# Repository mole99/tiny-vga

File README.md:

# Tiny VGA 

Tiny VGA is a Pmod peripheral designed for [Tiny Tapeout](https://tinytapeout.com/), but can of course also be used with any other Pmod compatible hardware such as certain FPGA boards.

View the schematic online using [KiCanvas](https://kicanvas.org/?github=https%3A%2F%2Fgithub.com%2Fmole99%2Ftiny-vga%2Fblob%2Fmain%2Fpcb%2Ftiny-vga.kicad_sch)!

**Why Yet Another Pmod VGA Peripheral?**

Tiny VGA only needs one Pmod connector to work. This means if you choose to use the output Pmod of the Tiny Tapeout PCB to connect to Tiny VGA, you still have the bidirectional and input Pmod available for other purposes.

It defines an interface for 2-bit per color VGA, so you can easily try other Tiny Tapeout designs that use the Tiny VGA pinout.

The board is designed in [KiCad](https://www.kicad.org/) and uses the [KiCAD JLCPCB tools](https://github.com/Bouni/kicad-jlcpcb-tools) to manage the assignment of components from the JLCPCB parts library.

## How Do I Get One? 

I do not sell Tiny VGAs, but you can order a few Tiny VGAs directly from PCB manufacturers for relatively little money. the cost per PCB gets cheaper if you order, say, ten at a time. You could give away the remaining Tiny VGAs to others who are located near you to help out the community :)

Search the Tiny Tapeout Discord server for others who could use one.

## Ordering Tiny VGA at JLCPCB

I have designed Tiny VGA so that it can be easily ordered fully-manufactured from JLCPCB. I am not sponsored or affiliated with JLCPCB in any way. If you would like to make it possible to produce Tiny VGA with other PCB manufacturers, you are welcome to contribute!

The [KiCAD JLCPCB tools](https://github.com/Bouni/kicad-jlcpcb-tools) needs to be installed to create the production files. Or you can use them right away under `pcb/jlcpcb/production_files/`.

1. Go to [JLCPCB](https://jlcpcb.com/) and create an account. 
2. Upload the gerber files from `pcb/jlcpcb/production_files/GERBER-tiny-vga.zip`.
3. You will get various options to choose from and a price offer. You don't really need to change anything, but you could change the quantity, choose a different color for the PCB and remove the order number.
3. Next, enable "PCB Assembly", keep the settings as they are and confirm. You will be forwarded to a new page with a view of the PCB. 
4. Click on "Next" and you will be prompted to upload the BOM and CPL file which you can find under `pcb/jlcpcb/production_files/BOM-tiny-vga.csv` and `pcb/jlcpcb/production_files/CPL-tiny-vga.csv`. 
5. The next page shows you all the parts that will be placed. 
6. Again, "Next" will lead you to the component placement page where you can confirm the placement of the parts. Here you might need to rotate some of the components.
7. Click on "Next" and you will get your quote for the assembled PCBs. Proceed to the checkout and you are done :D

## Tiny VGA Pinout

Pin numbering according to Pmod specification.

| Pin | Signal | Pin | Signal |
| :-: | :----: | :-: | :----: |
| top row    | | bottom row | |
| 1   | R1     | 7   | R0     |
| 2   | G1     | 8   | G0     |
| 3   | B1     | 9   | B0     |
| 4   | VS     | 10  | HS     |
| 5   | GND    | 11  | GND    |
| 6   | VCC    | 12  | VCC    |

> [!NOTE]  
> R0, G0, B0 are the least significant bits\
> R1, G1, B1 are the most significant bits\
> VS is the vertical sync\
> HS is the horizontal sync\
> VCC must be 3V3

## Board Images

### v1.0

Tiny VGA v1.0 board manufactured by JLCPCB, including SMD components (THT connectors manually soldered).

|          |      |
|--------------|-----------|
|  |       |

### v1.2

Tiny VGA v1.2 board manufactured by JLCPCB, including SMD components and THT connectors.

|          |      |
|--------------|-----------|
|  |       |

## Demo

The demo output is 800x600 SVGA and the quality is excellent in real life.

## License

This work is licensed under a
[Creative Commons Attribution-ShareAlike 4.0 International License][cc-by-sa].

[cc-by-sa]: http://creativecommons.org/licenses/by-sa/4.0/

Copyright (c) Leo Moser

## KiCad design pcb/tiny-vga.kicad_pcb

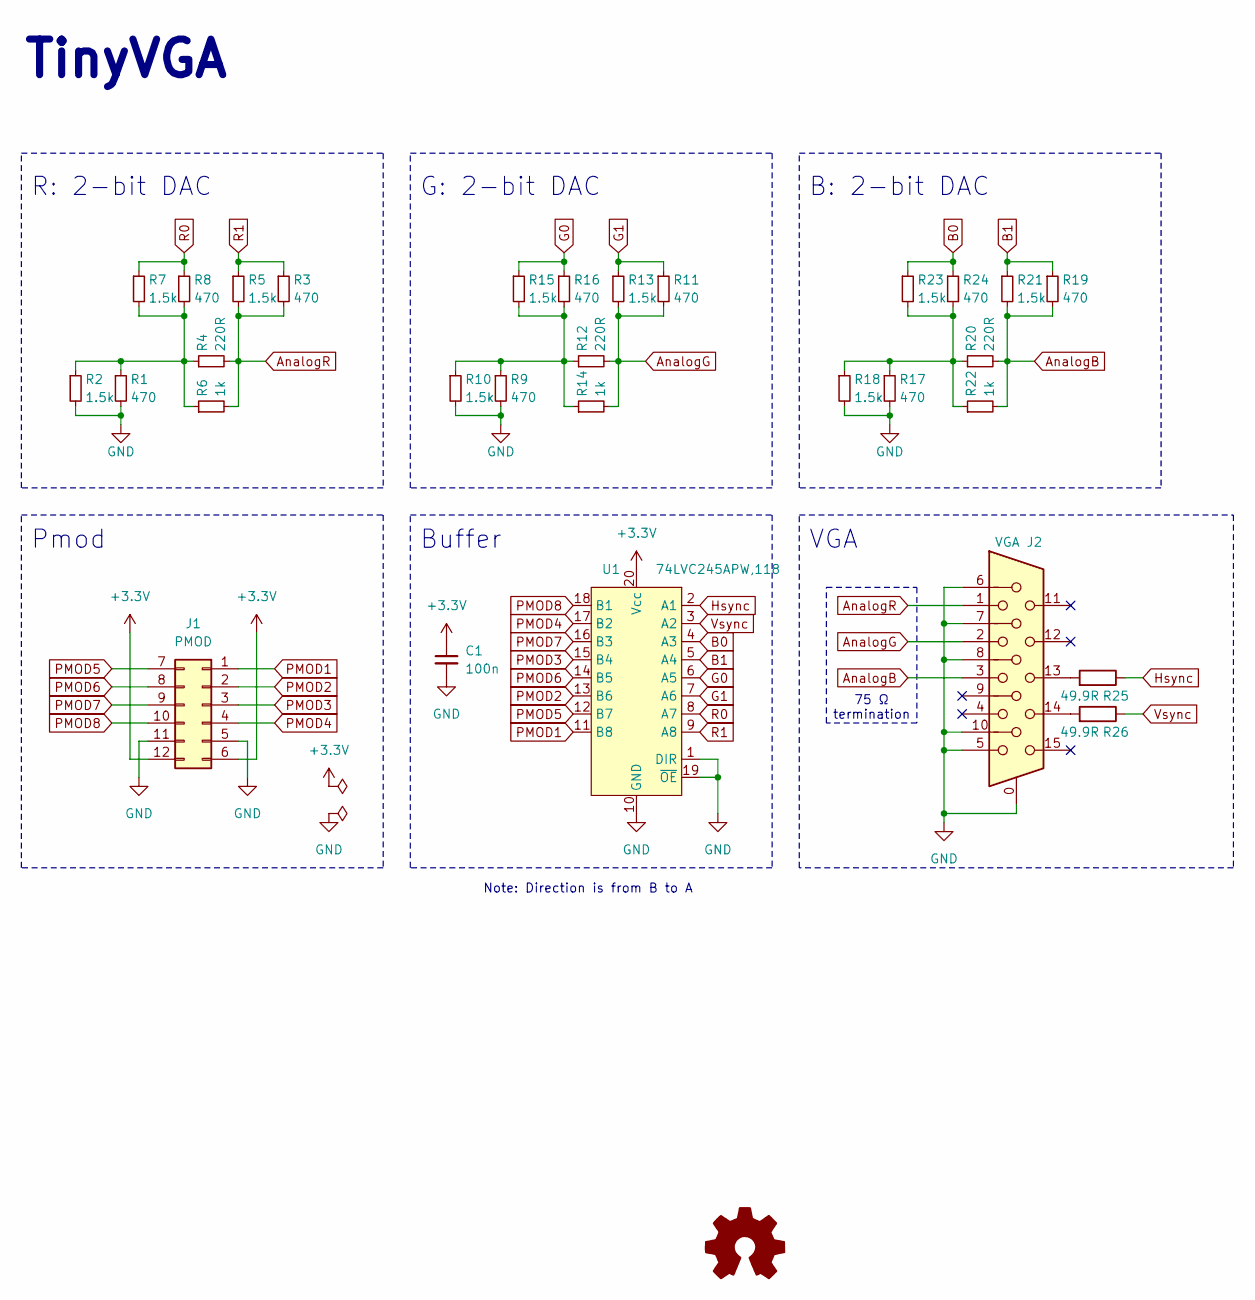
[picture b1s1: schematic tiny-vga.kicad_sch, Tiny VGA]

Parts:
C1: 100n; C_0603_1608Metric; MPN CGA3E3X7S2A104M080AB; LCSC C14663
J1: PMOD; PinHeader_2x06_P2.54mm_Horizontal; MPN 826634-6; LCSC C2935938
J2: VGA; DSUB-15-HD_Female_Horizontal_P2.29x1.98mm_EdgePinOffset8.35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; MPN L77HDE15SD1CH4FVGA; LCSC C138387
R1, R3, R8, R9, R11, R16, R17, R19, R24: 470; R_0402_1005Metric; MPN RCC0402470RFKED; LCSC C25117
R2, R5, R7, R10, R13, R15, R18, R21, R23: 1.5k; R_0402_1005Metric; MPN RCC04021K50FKED; LCSC C25867
R4, R12, R20: 220R; R_0402_1005Metric; MPN RCS0402220RFKED; LCSC C25091
R6, R14, R22: 1k; R_0402_1005Metric; MPN CRCW04021K00FKED; LCSC C11702
R25, R26: 49.9R; R_0402_1005Metric; MPN ERJ-2RKF49R9X; LCSC C25120
U1: 74LVC245APW,118; TSSOP-20_4.4x6.5mm_P0.65mm; MPN 74LVC245APW,118; LCSC C6082

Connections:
+3.3V: C1.1, J1.6, J1.12, U1.20 (Vcc)
AnalogB: J2.3, R19.2, R20.2, R21.2, R22.2
AnalogG: J2.2, R11.2, R12.2, R13.2, R14.2
AnalogR: J2.1, R3.2, R4.2, R5.2, R6.2
B0: R23.1, R24.1, U1.4 (A3)
B1: R19.1, R21.1, U1.5 (A4)
G0: R15.1, R16.1, U1.6 (A5)
G1: R11.1, R13.1, U1.7 (A6)
GND: C1.2, J1.5, J1.11, J2.0, J2.5, J2.6, J2.7, J2.8, J2.10, R1.2, R2.2, R9.2, R10.2, R17.2, R18.2, U1.1 (DIR), U1.10 (GND), U1.19 (~OE)
Hsync: R25.1, U1.2 (A1)
unnamed: J2.13, R25.2
unnamed: J2.14, R26.2
unnamed: R1.1, R2.1, R4.1, R6.1, R7.2, R8.2
unnamed: R9.1, R10.1, R12.1, R14.1, R15.2, R16.2
unnamed: R17.1, R18.1, R20.1, R22.1, R23.2, R24.2
PMOD1: J1.1, U1.11 (B8)
PMOD2: J1.2, U1.13 (B6)
PMOD3: J1.3, U1.15 (B4)
PMOD4: J1.4, U1.17 (B2)
PMOD5: J1.7, U1.12 (B7)
PMOD6: J1.8, U1.14 (B5)
PMOD7: J1.9, U1.16 (B3)
PMOD8: J1.10, U1.18 (B1)
R0: R7.1, R8.1, U1.8 (A7)
R1: R3.1, R5.1, U1.9 (A8)
Vsync: R26.1, U1.3 (A2)

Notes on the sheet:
G: 2-bit DAC
Pmod
75 Ω termination
R: 2-bit DAC
TinyVGA
VGA
B: 2-bit DAC
Note: Direction is from B to A
Buffer

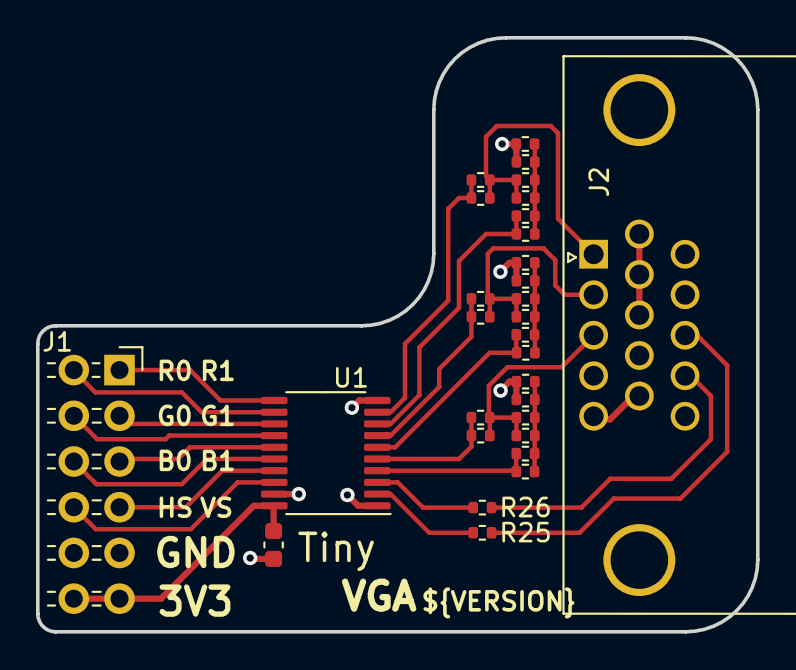
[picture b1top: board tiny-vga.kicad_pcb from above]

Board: 2 copper layers, 40.0 x 33.0 mm, 30 parts (0 on the bottom side), 26 nets.

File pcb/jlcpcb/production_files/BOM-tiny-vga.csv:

Comment,Designator,Footprint,LCSC
1k,"R14,R22,R6",R_0402_1005Metric,C11702
VGA,J2,VGA-002,C138387
100n,C1,C_0603_1608Metric,C14663
220R,"R12,R20,R4",R_0402_1005Metric,C25091
470,"R1,R11,R16,R17,R19,R24,R3,R8,R9",R_0402_1005Metric,C25117
49.9R,"R25,R26",R_0402_1005Metric,C25120
1.5k,"R10,R13,R15,R18,R2,R21,R23,R5,R7",R_0402_1005Metric,C25867
PMOD,J1,PinHeader_2x06_P2.54mm_Horizontal,C2935938
"74LVC245APW,118",U1,TSSOP-20_4.4x6.5mm_P0.65mm,C6082

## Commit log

2023-10-23 Tiny VGA v1.0
2023-10-23 Update pinout
2023-10-23 Update comments
2023-10-23 Add BOM and CPL
2023-11-19 Update parts for aisler
2023-12-09 Add AISLER support
2024-02-03 Update trace widths
2024-06-02 Final v1.2, tested and working
2024-09-04 Add board render and link to schematic
2024-09-04 Fix typo

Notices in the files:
README.md:
License: CC BY-SA 4.0
